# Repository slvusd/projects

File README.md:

# Projects

The purpose of this repo is to sync teacher and student work to a repo
so it can be shared and so it will not get lost.

To add a new computer to this repo, run these commands:

    git config --global user.name slvusd-gitbot
    git config --global user.email "ebrown+gitbot@slvusd.org"
    git config --global credential.helper store

Then from pi's home directory, run

    git -c credential.helper= clone https://github.com/slvusd/projects.git src

You will be prompted for the username (slvusd-github) and password. Get the
password (token) from Mr. Brown.

You need to run `$HOME/src/git_sync.sh` once from the
command line and enter the same credentials in order
to have the credentials cached for cron.

Finally, run `crontab -e` and add the following entry:

    */5 * * * * /home/pi/src/git_sync.sh

That's it!

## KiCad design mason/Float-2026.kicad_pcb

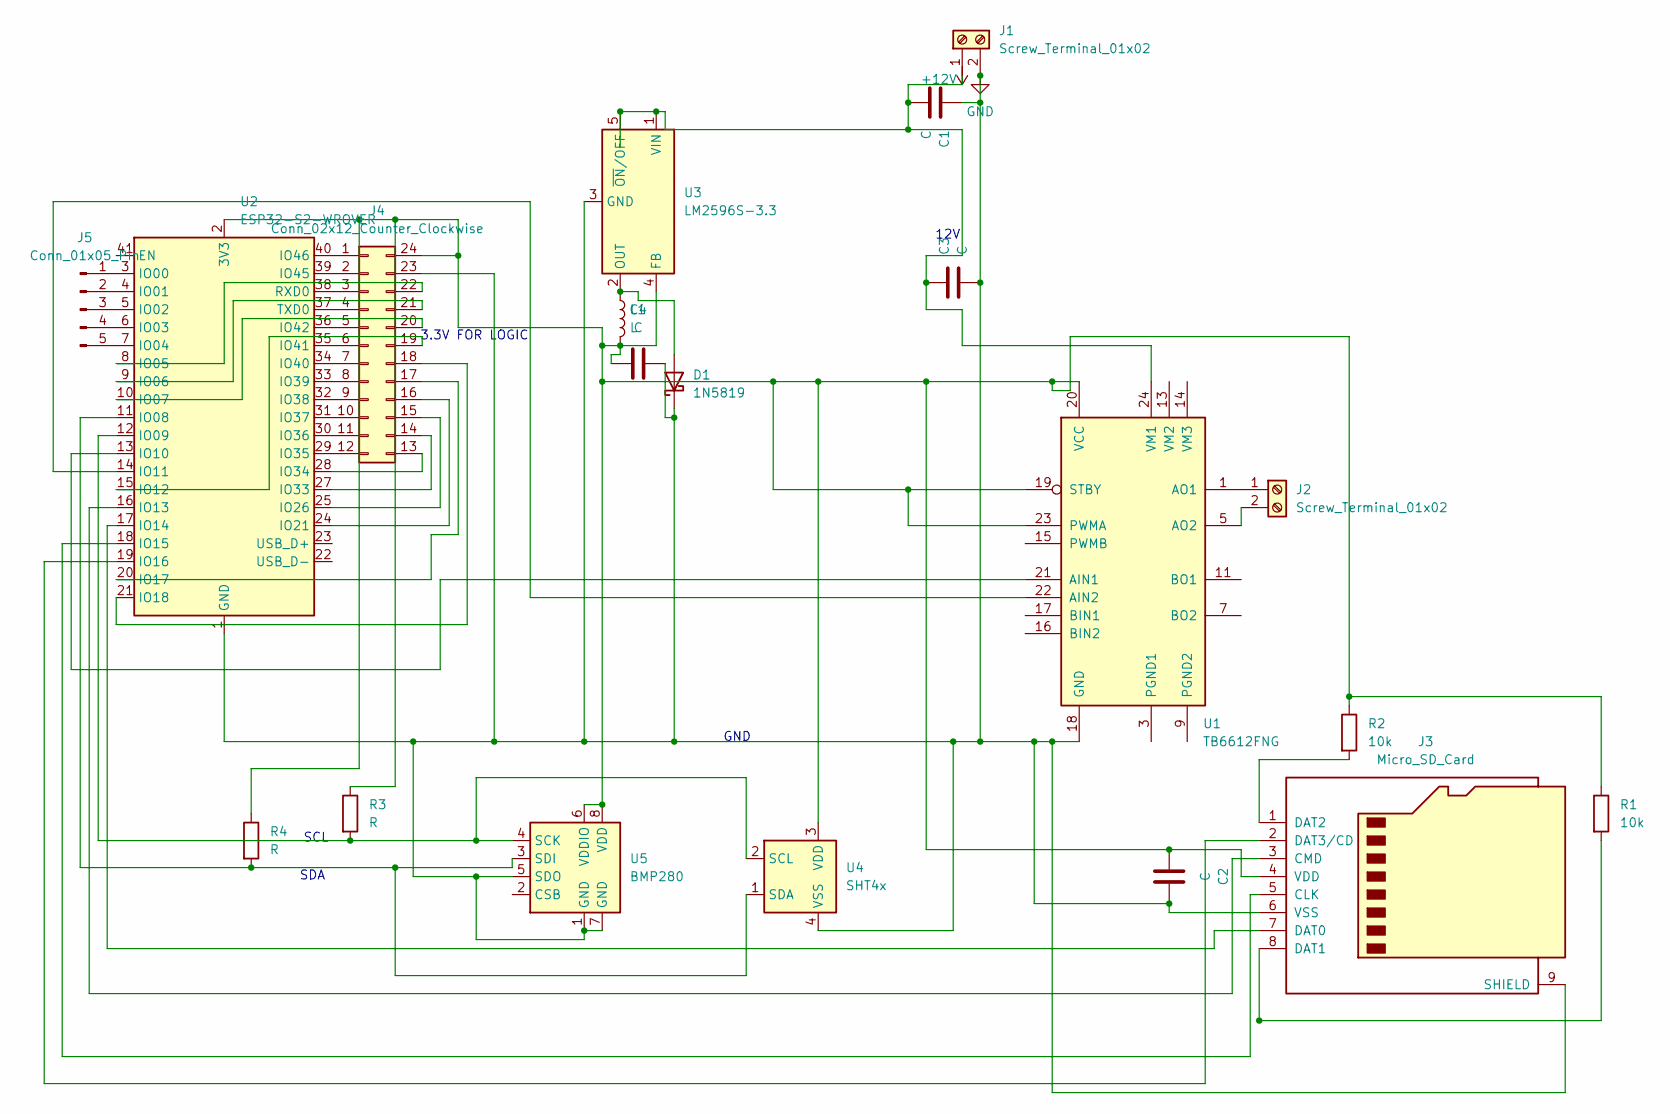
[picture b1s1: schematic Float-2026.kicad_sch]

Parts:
C1, C2, C3, C4: C; C_Axial_L3.8mm_D2.6mm_P7.50mm_Horizontal
D1: 1N5819; D_DO-41_SOD81_P10.16mm_Horizontal
J1, J2: Screw_Terminal_01x02; TerminalBlock_Ningbo-Kagnex_HB9500M_1x02_P9.5mm
J3: Micro_SD_Card; microSD_HC_Wuerth_693072010801
J4: Conn_02x12_Counter_Clockwise; PinHeader_2x12_P2.00mm_Vertical
J5: Conn_01x05_Pin; PinHeader_1x05_P2.00mm_Vertical
L1: L; L_Axial_L5.0mm_D3.6mm_P10.00mm_Horizontal_Murata_BL01RN1A2A2
R1, R2: 10k; R_Axial_DIN0204_L3.6mm_D1.6mm_P1.90mm_Vertical
R3, R4: R; R_Axial_DIN0204_L3.6mm_D1.6mm_P1.90mm_Vertical
U1: TB6612FNG; SSOP-24_5.3x8.2mm_P0.65mm
U2: ESP32-S2-WROVER
U3: LM2596S-3.3; TO-263-5_TabPin3
U4: SHT4x; Sensirion_DFN-4_1.5x1.5mm_P0.8mm_SHT4x_NoCentralPad
U5: BMP280; Bosch_LGA-8_2x2.5mm_P0.65mm_ClockwisePinNumbering

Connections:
GND: C1.1, C2.2, C3.2, C4.2, D1.1 (K), J1.2, J3.6 (VSS), J3.9 (SHIELD), J4.23, U1.18 (GND), U2.1 (GND), U2.26 (GND), U2.42 (GND), U2.43 (GND), U3.3 (GND), U4.4 (VSS), U5.1 (GND), U5.5 (SDO), U5.7 (GND)
unnamed: D1.2 (A), L1.1, U3.2 (OUT)
unnamed: C1.2, C3.1, J1.1, U1.24 (VM1), U3.1 (VIN), U3.5 (~ON/OFF)
unnamed: J2.1, U1.1 (AO1), U1.2 (AO1)
unnamed: J2.2, U1.5 (AO2), U1.6 (AO2)
unnamed: J3.5 (CLK), U2.18 (IO15)
unnamed: J3.3 (CMD), U2.16 (IO13)
unnamed: J3.7 (DAT0), U2.17 (IO14)
unnamed: J3.8 (DAT1), R1.2
unnamed: J3.1 (DAT2), R2.2
unnamed: J3.2 (DAT3/CD), U2.19 (IO16)
unnamed: C2.1, C4.1, J3.4 (VDD), J4.24, L1.2, R1.1, R2.1, R3.1, R4.1, U1.19 (STBY), U1.20 (VCC), U1.23 (PWMA), U2.2 (3V3), U3.4 (FB), U4.3 (VDD), U5.6 (VDDIO), U5.8 (VDD)
unnamed: J4.1, U2.40 (IO46)
unnamed: J4.2, U2.39 (IO45)
unnamed: J4.3, U2.38 (RXD0)
unnamed: J4.4, U2.37 (TXD0)
unnamed: J4.5, U2.36 (IO42)
unnamed: J4.6, U2.35 (IO41)
unnamed: J4.7, U2.34 (IO40)
unnamed: J4.8, U2.33 (IO39)
unnamed: J4.9, U2.32 (IO38)
unnamed: J4.10, U2.31 (IO37)
unnamed: J4.11, U2.30 (IO36)
unnamed: J4.12, U2.29 (IO35)
unnamed: J4.13, U2.28 (IO34)
unnamed: J4.14, U2.27 (IO33)
unnamed: J4.15, U2.25 (IO26)
unnamed: J4.16, U2.24 (IO21)
unnamed: J4.17, U2.20 (IO17)
unnamed: J4.18, U2.21 (IO18)
unnamed: J4.19, U2.15 (IO12)
unnamed: J4.20, U2.10 (IO07)
unnamed: J4.21, U2.9 (IO06)
unnamed: J4.22, U2.8 (IO05)
unnamed: J5.1, U2.3 (IO00)
unnamed: J5.2, U2.4 (IO01)
unnamed: J5.3, U2.5 (IO02)
unnamed: J5.4, U2.6 (IO03)
unnamed: J5.5, U2.7 (IO04)
unnamed: U1.21 (AIN1), U2.13 (IO10)
unnamed: U1.22 (AIN2), U2.14 (IO11)
unnamed: U1.11 (BO1), U1.12 (BO1)
unnamed: U1.7 (BO2), U1.8 (BO2)
unnamed: U1.3 (PGND1), U1.4 (PGND1)
unnamed: U1.9 (PGND2), U1.10 (PGND2)
unnamed: R4.2, U2.11 (IO08), U4.1 (SDA), U5.3 (SDI)
unnamed: R3.2, U2.12 (IO09), U4.2 (SCL), U5.4 (SCK)

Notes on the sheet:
SCL
12V
GND
SDA
3.3V FOR LOGIC

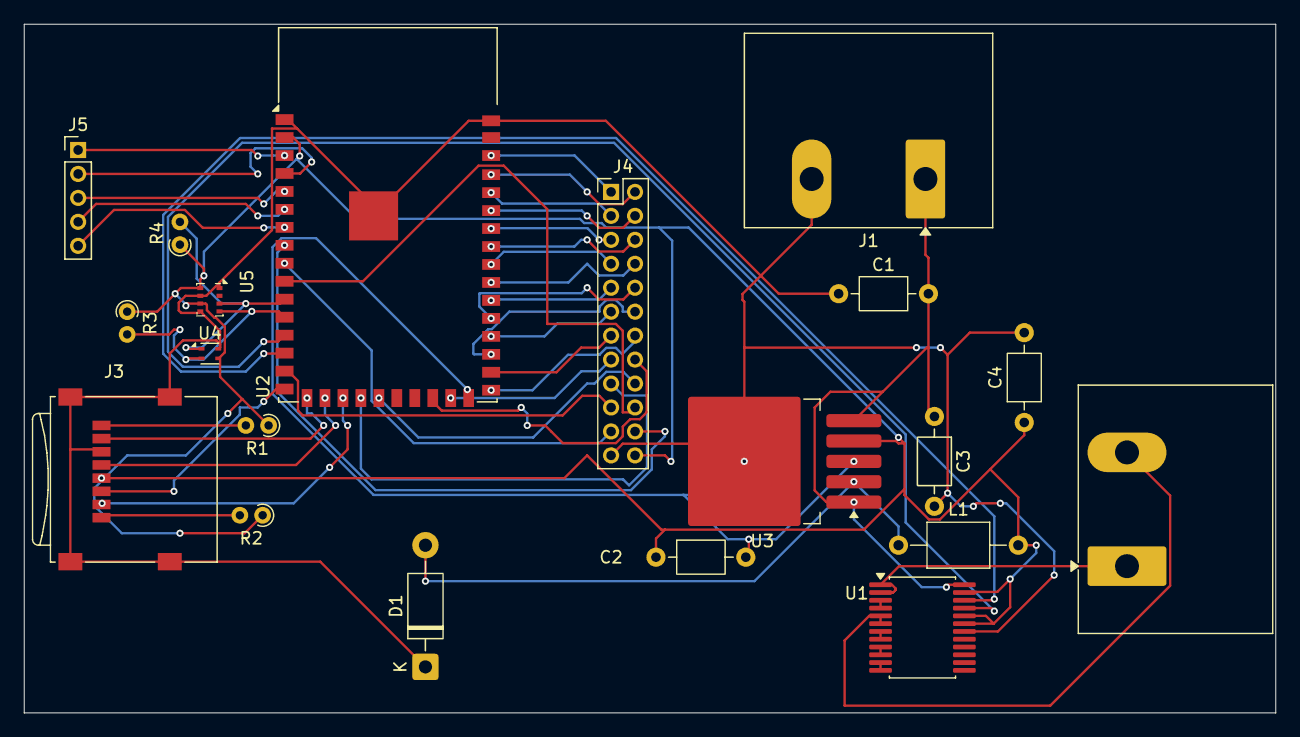
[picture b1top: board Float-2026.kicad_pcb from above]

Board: 2 copper layers, 104.5 x 57.5 mm, 20 parts (0 on the bottom side), 47 nets.

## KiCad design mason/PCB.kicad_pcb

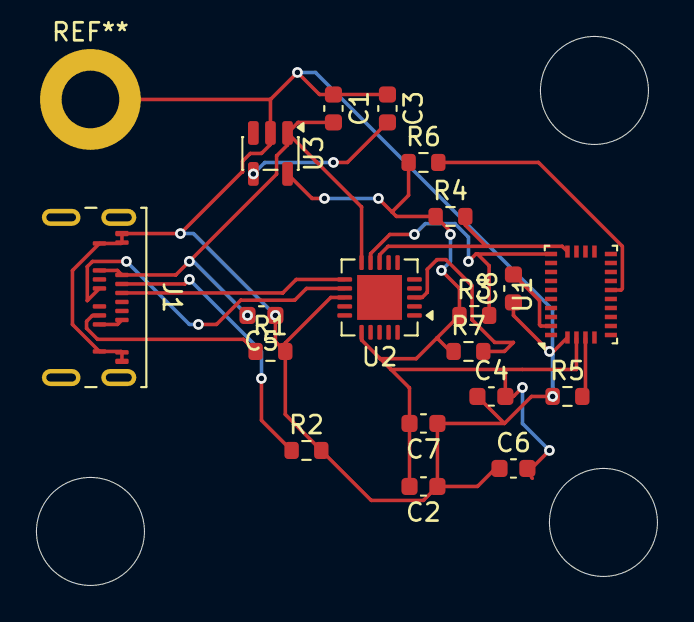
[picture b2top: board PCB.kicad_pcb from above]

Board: 2 copper layers, 34.5 x 30.5 mm, 19 parts (0 on the bottom side), 14 nets.

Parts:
C1, C2: 1µF; C_0603_1608Metric
C3: 100nF; C_0603_1608Metric
C4: 10µF; C_0603_1608Metric
C5, C6, C7, C8: 0.1µF; C_0603_1608Metric
J1: USB_C_Receptacle_USB2.0_14P; USB_C_Receptacle_Amphenol_124019772112A
R1, R2: 5.1k; R_0603_1608Metric
R3, R4: 4.7k; R_0603_1608Metric
R5, R6, R7: 10k; R_0603_1608Metric
U1: BNO055; LGA-28_5.2x3.8mm_P0.5mm
U2: MCP2221AxML; QFN-20-1EP_4x4mm_P0.5mm_EP2.5x2.5mm
U3: LP2985-3.3; SOT-23-5

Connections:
unnamed: C1.1, C2.1, C3.1, C4.1, C5.1, C6.1, C7.1, C8.1, J1.A1 (GND), J1.A12 (GND), J1.B1 (GND), J1.B12 (GND), R1.2, R2.2, R5.1, U1.2 (GND), U2.13 (VSS), U3.2 (GND)
unnamed: J1.A5 (CC1), R2.1
unnamed: J1.B5 (CC2), R1.1
unnamed: R3.2, U1.20 (COM0), U2.9 (SCL)
unnamed: R4.2, U1.19 (COM1), U2.8 (SDA)
unnamed: C2.2, C4.2, C6.2, C7.2, R3.1, R4.1, R6.1, R7.1, U1.3 (VDD), U2.16 (VDD), U3.5 (VOUT)
unnamed: C8.2, U1.28 (VDDIO)
unnamed: R5.2, U1.4 (~BOOT_LOAD_PIN)
unnamed: R6.2, U1.11 (~RESET)
unnamed: J1.B7 (D-), U2.12 (D+)
unnamed: J1.A6 (D+), U2.11 (D-)
unnamed: C1.2, C5.2, J1.A4 (VBUS), J1.A9 (VBUS), J1.B4 (VBUS), J1.B9 (VBUS), U2.10 (VUSB), U3.1 (VIN)
unnamed: R7.2, U2.3 (~RST)
unnamed: C3.2, U3.4 (BP)

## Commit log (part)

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2024-11-22 Auto-sync: Thu 21 Nov 21:04:49 PST 2024
2024-11-22 Update README.md
    Add instructions for adding new computers.
2024-11-22 Auto-sync: Thu 21 Nov 21:25:02 PST 2024
2024-11-22 Auto-sync: Thu 21 Nov 22:15:02 PST 2024
2024-11-22 Auto-sync: Thu 21 Nov 22:17:30 PST 2024
2024-11-22 Update instructions
2024-11-22 Auto-sync: Fri 22 Nov 13:15:03 PST 2024
2024-11-25 Auto-sync: Mon 25 Nov 00:40:01 PST 2024
2024-11-25 Auto-sync: Mon 25 Nov 00:50:02 PST 2024
2024-11-25 Auto-sync: Mon 25 Nov 00:55:01 PST 2024
2024-11-25 Auto-sync: Mon 25 Nov 01:00:02 PST 2024
2024-11-25 Auto-sync: Mon 25 Nov 01:05:01 PST 2024
2024-11-25 Auto-sync: Mon 25 Nov 01:10:01 PST 2024
2024-11-25 Auto-sync: Mon 25 Nov 01:15:02 PST 2024
2024-11-25 Auto-sync: Mon 25 Nov 01:25:01 PST 2024
2024-11-25 Auto-sync: Mon 25 Nov 01:30:02 PST 2024
2024-11-25 Auto-sync: Mon 25 Nov 01:35:19 PST 2024
2024-11-25 Auto-sync: Mon 25 Nov 02:05:02 PST 2024
2024-11-25 Auto-sync: Mon 25 Nov 02:10:02 PST 2024
2024-11-25 Auto-sync: Mon 25 Nov 02:15:02 PST 2024
2024-11-25 Auto-sync: Mon 25 Nov 02:20:02 PST 2024
2024-11-25 Auto-sync: Mon 25 Nov 02:45:02 PST 2024
2024-11-25 Auto-sync: Mon 25 Nov 02:50:02 PST 2024
2024-11-25 Auto-sync: Mon 25 Nov 02:55:02 PST 2024
2024-11-25 Auto-sync: Mon 25 Nov 03:00:02 PST 2024
2024-11-25 Auto-sync: Mon 25 Nov 03:05:02 PST 2024
2024-11-25 Auto-sync: Mon 25 Nov 03:10:02 PST 2024
2024-11-25 Auto-sync: Mon 25 Nov 03:15:02 PST 2024
2024-11-26 Auto-sync from slvpi3-1: Mon 25 Nov 16:20:03 PST 2024
2024-11-26 Auto-sync from slvpi3-1: Mon 25 Nov 16:30:02 PST 2024
2024-11-26 Auto-sync from slvpi3-1: Mon 25 Nov 16:35:02 PST 2024
2024-11-26 Auto-sync from slvpi3-1: Mon 25 Nov 16:40:03 PST 2024
2024-11-26 Auto-sync from slvpi4-2: Mon 25 Nov 17:05:03 PST 2024
2024-11-26 Auto-sync from slvpi4-2: Mon 25 Nov 17:10:02 PST 2024
2024-11-26 Auto-sync from slvpi4-2: Mon 25 Nov 17:55:02 PST 2024
2024-11-26 Auto-sync from slvpi3-1: Mon 25 Nov 18:00:03 PST 2024
2024-11-26 Auto-sync from slvpi3-1: Mon 25 Nov 18:05:02 PST 2024
2024-11-26 Auto-sync from slvpi3-1: Mon 25 Nov 18:10:02 PST 2024
2024-11-26 Auto-sync from slvpi3-1: Mon 25 Nov 18:15:02 PST 2024
2024-11-26 Auto-sync from slvpi3-1: Mon 25 Nov 18:20:02 PST 2024
2024-11-26 Auto-sync from slvpi4-2: Mon 25 Nov 18:36:52 PST 2024
2024-11-26 Auto-sync from slvpi4-2: Mon 25 Nov 18:45:02 PST 2024
2024-11-26 Auto-sync from slvpi4-2: Mon 25 Nov 18:50:02 PST 2024
2024-11-26 Auto-sync from slvpi4-2: Mon 25 Nov 19:05:01 PST 2024
2024-11-26 Auto-sync from slvpi4-2: Mon 25 Nov 20:35:03 PST 2024
2024-11-26 Auto-sync from slvpi4-2: Mon 25 Nov 20:40:02 PST 2024
2024-11-26 Auto-sync from slvpi4-2: Mon 25 Nov 20:55:02 PST 2024
2024-11-26 Auto-sync from slvpi4-2: Mon 25 Nov 21:00:02 PST 2024
2024-11-26 Auto-sync from slvpi4-2: Mon 25 Nov 21:10:02 PST 2024
2024-11-26 Auto-sync from slvpi4-2: Mon 25 Nov 21:15:01 PST 2024
2024-11-26 Auto-sync from slvpi4-2: Mon 25 Nov 21:20:02 PST 2024
2024-11-26 Auto-sync from slvpi4-2: Mon 25 Nov 21:25:01 PST 2024
2024-11-26 Auto-sync from slvpi4-2: Mon 25 Nov 21:30:02 PST 2024
2024-11-26 Auto-sync from slvpi3-1: Tue 26 Nov 12:25:02 PST 2024
2024-11-26 Auto-sync from slvpi3-1: Tue 26 Nov 12:30:04 PST 2024
2024-11-26 Auto-sync from slvpi3-1: Tue 26 Nov 12:40:02 PST 2024
2024-11-26 Auto-sync from slvpi3-1: Tue 26 Nov 12:45:02 PST 2024
2024-11-26 Auto-sync from slvpi3-1: Tue 26 Nov 12:55:03 PST 2024
2024-11-26 Auto-sync from slvpi3-1: Tue 26 Nov 13:00:03 PST 2024
2024-11-26 Auto-sync from slvpi3-1: Tue 26 Nov 13:10:04 PST 2024
2024-11-26 Auto-sync from slvpi3-1: Tue 26 Nov 13:25:02 PST 2024
2024-11-26 Auto-sync from slvpi3-1: Tue 26 Nov 13:30:02 PST 2024
2024-11-26 Auto-sync from slvpi3-1: Tue 26 Nov 13:55:02 PST 2024
2024-11-26 Auto-sync from slvpi3-1: Tue 26 Nov 14:05:02 PST 2024
2024-11-26 Auto-sync from slvpi3-1: Tue 26 Nov 14:10:02 PST 2024
2024-11-26 Auto-sync from slvpi3-1: Tue 26 Nov 14:25:02 PST 2024
2024-11-27 Auto-sync from slvpi4-2: Tue 26 Nov 18:35:02 PST 2024
2024-11-27 Auto-sync from slvpi4-2: Tue 26 Nov 21:45:03 PST 2024
2024-11-27 Auto-sync from slvpi4-2: Tue 26 Nov 21:55:02 PST 2024
2024-11-27 Auto-sync from slvpi4-2: Tue 26 Nov 22:00:02 PST 2024
2024-11-27 Documentaiton based on today's work
2024-11-27 Auto-sync from slvpi5: Wed 27 Nov 09:35:02 PST 2024
2024-11-27 Auto-sync from slvpi5: Wed 27 Nov 09:40:01 PST 2024
2024-11-28 Auto-sync from slvpi4-2: Wed 27 Nov 22:20:05 PST 2024
2024-11-28 Auto-sync from slvpi4-2: Wed 27 Nov 22:25:02 PST 2024
2024-11-28 Auto-sync from slvpi4-2: Wed 27 Nov 22:35:02 PST 2024
2024-11-28 Auto-sync from slvpi4-2: Wed 27 Nov 22:40:02 PST 2024
2024-11-29 Add circuit diagram to variable_motor
2024-11-30 Auto-sync from slvpizt1: Sat 30 Nov 10:40:19 PST 2024
2024-11-30 Auto-sync from slvpizt1: Sat 30 Nov 10:45:04 PST 2024
2024-11-30 Auto-sync from slvpizt1: Sat 30 Nov 10:50:04 PST 2024
2024-11-30 Auto-sync from slvpizt1: Sat 30 Nov 11:15:03 PST 2024
2024-11-30 Auto-sync from slvpizt1: Sat 30 Nov 11:25:12 PST 2024
2024-11-30 Auto-sync from slvpizt1: Sat 30 Nov 11:30:04 PST 2024
2024-11-30 Auto-sync from slvpizt1: Sat 30 Nov 11:35:05 PST 2024
2024-11-30 Auto-sync from slvpizt1: Sat 30 Nov 11:40:11 PST 2024
2024-11-30 Auto-sync from slvpizt1: Sat 30 Nov 13:10:10 PST 2024
2024-12-01 Auto-sync from slvpizt1: Sun 1 Dec 08:55:05 PST 2024
2024-12-02 Auto-sync from slvpi5: Sun 1 Dec 17:05:01 PST 2024
2024-12-09 Auto-sync from slvpi4-2: Mon 9 Dec 13:40:05 PST 2024
2024-12-09 Auto-sync from slvpi4-2: Mon 9 Dec 13:45:04 PST 2024
2024-12-09 Auto-sync from slvpi4-2: Mon 9 Dec 13:50:04 PST 2024
2024-12-09 Auto-sync from slvpi4-2: Mon 9 Dec 13:55:05 PST 2024
2024-12-10 Auto-sync from slvpi4-2: Tue 10 Dec 13:50:09 PST 2024
2024-12-10 Auto-sync from slvpi4-2: Tue 10 Dec 14:00:06 PST 2024
2024-12-10 Auto-sync from slvpi4-2: Tue 10 Dec 14:05:04 PST 2024
2024-12-10 Auto-sync from slvpi4-2: Tue 10 Dec 14:45:04 PST 2024
2024-12-10 Auto-sync from slvpi4-2: Tue 10 Dec 14:50:04 PST 2024
2024-12-11 Auto-sync from slvpi4-2: Tue 10 Dec 17:35:16 PST 2024
2024-12-11 Auto-sync from slvpizt1: Tue 10 Dec 17:40:02 PST 2024
2024-12-13 Auto-sync from slvpi4-2: Fri 13 Dec 09:35:03 PST 2024
2024-12-13 Auto-sync from slvpi4-2: Fri 13 Dec 14:35:04 PST 2024
2024-12-13 Auto-sync from slvpi4-2: Fri 13 Dec 14:50:05 PST 2024
2024-12-25 Auto-sync from slvpi5: Wed 25 Dec 13:55:01 PST 2024
2024-12-25 Auto-sync from slvpi5: Wed 25 Dec 14:00:02 PST 2024
2025-01-16 Auto-sync from slvpi4-2: Thu 16 Jan 14:35:04 PST 2025
2025-01-16 Auto-sync from slvpi4-2: Thu 16 Jan 14:40:04 PST 2025
2025-01-16 Auto-sync from slvpi4-2: Thu 16 Jan 14:45:09 PST 2025
2025-01-21 Auto-sync from slvpi4-2: Tue 21 Jan 11:40:05 PST 2025
2025-01-21 Auto-sync from slvpi4-2: Tue 21 Jan 12:55:04 PST 2025
2025-01-21 Auto-sync from slvpi4-2: Tue 21 Jan 13:05:04 PST 2025
2025-01-21 Auto-sync from slvpi4-2: Tue 21 Jan 13:55:04 PST 2025
2025-01-21 Auto-sync from slvpi4-2: Tue 21 Jan 14:00:04 PST 2025
2025-01-21 Auto-sync from slvpi4-2: Tue 21 Jan 14:05:04 PST 2025
2025-01-21 Auto-sync from slvpi4-2: Tue 21 Jan 14:10:04 PST 2025
2025-01-21 Auto-sync from slvpi4-2: Tue 21 Jan 14:25:04 PST 2025
2025-01-21 Auto-sync from slvpi4-2: Tue 21 Jan 14:35:04 PST 2025
2025-01-21 Auto-sync from slvpi4-2: Tue 21 Jan 14:40:04 PST 2025
2025-01-21 Auto-sync from slvpi4-2: Tue 21 Jan 14:45:04 PST 2025
2025-01-21 Auto-sync from slvpi4-2: Tue 21 Jan 14:50:04 PST 2025
2025-01-23 Auto-sync from slvpi4-2: Thu 23 Jan 12:50:06 PST 2025
2025-01-23 Auto-sync from slvpi4-2: Thu 23 Jan 12:55:05 PST 2025
2025-01-23 Auto-sync from slvpi4-2: Thu 23 Jan 13:00:04 PST 2025
2025-01-23 Auto-sync from slvpi4-2: Thu 23 Jan 13:55:04 PST 2025
2025-01-23 Auto-sync from slvpi4-2: Thu 23 Jan 14:00:06 PST 2025
2025-01-23 Auto-sync from slvpi4-2: Thu 23 Jan 14:05:04 PST 2025
2025-01-23 Auto-sync from slvpi4-2: Thu 23 Jan 14:10:04 PST 2025
2025-01-23 Auto-sync from slvpi4-2: Thu 23 Jan 14:25:04 PST 2025
2025-01-23 Auto-sync from slvpi4-2: Thu 23 Jan 14:30:04 PST 2025
2025-01-23 Auto-sync from slvpi4-2: Thu 23 Jan 14:45:04 PST 2025
2025-01-24 Auto-sync from slvpi4-2: Fri 24 Jan 13:00:04 PST 2025
2025-01-24 Auto-sync from slvpi4-2: Fri 24 Jan 13:10:04 PST 2025
2025-01-24 Auto-sync from slvpi4-2: Fri 24 Jan 13:15:04 PST 2025
2025-01-24 Auto-sync from slvpi4-2: Fri 24 Jan 13:20:04 PST 2025
2025-01-24 Auto-sync from slvpi4-2: Fri 24 Jan 13:25:04 PST 2025
2025-01-24 Auto-sync from slvpi4-2: Fri 24 Jan 13:30:06 PST 2025
2025-01-24 Auto-sync from slvpi4-2: Fri 24 Jan 13:40:05 PST 2025
2025-01-24 Auto-sync from slvpi4-2: Fri 24 Jan 13:45:05 PST 2025
2025-01-24 Auto-sync from slvpi4-2: Fri 24 Jan 14:45:04 PST 2025
2025-01-24 Auto-sync from slvpi4-2: Fri 24 Jan 14:50:04 PST 2025
2025-01-31 Auto-sync from slvpi4-2: Fri 31 Jan 13:10:05 PST 2025
2025-01-31 Auto-sync from slvpi4-2: Fri 31 Jan 13:15:05 PST 2025
2025-01-31 Auto-sync from slvpi4-2: Fri 31 Jan 13:40:04 PST 2025
2025-01-31 Auto-sync from slvpi4-2: Fri 31 Jan 14:05:04 PST 2025
2025-01-31 Auto-sync from slvpi4-2: Fri 31 Jan 14:50:05 PST 2025
2025-02-03 Auto-sync from slvpi4-2: Mon 3 Feb 13:20:04 PST 2025
2025-02-03 Auto-sync from slvpi4-2: Mon 3 Feb 13:25:04 PST 2025
2025-02-03 Auto-sync from slvpi4-2: Mon 3 Feb 13:35:06 PST 2025
2025-02-03 Auto-sync from slvpi4-2: Mon 3 Feb 13:40:05 PST 2025
2025-02-03 Auto-sync from slvpi4-2: Mon 3 Feb 13:45:04 PST 2025
2025-02-03 Auto-sync from slvpi4-2: Mon 3 Feb 13:55:09 PST 2025
2025-04-30 Auto-sync from slvpi4-2: Wed 30 Apr 14:00:04 PDT 2025
2025-04-30 Auto-sync from slvpi4-2: Wed 30 Apr 14:05:04 PDT 2025
2025-04-30 Auto-sync from slvpi4-2: Wed 30 Apr 14:20:04 PDT 2025
2025-05-28 Auto-sync from slvpi4-2: Wed 28 May 12:55:05 PDT 2025
2025-05-28 Auto-sync from slvpi4-2: Wed 28 May 13:00:04 PDT 2025
2025-05-28 Auto-sync from slvpi4-2: Wed 28 May 13:05:04 PDT 2025
2026-01-19 Auto-sync from pi47: Mon 19 Jan 13:40:02 PST 2026
2026-01-20 Auto-sync from piz0: Mon 19 Jan 21:00:03 PST 2026
2026-01-20 Auto-sync from pi07: Mon Jan 19 21:05:12 PST 2026
2026-01-20 Auto-sync from pi07: Mon Jan 19 21:10:14 PST 2026
2026-01-20 Auto-sync from pi07: Mon Jan 19 21:15:06 PST 2026
2026-01-20 Auto-sync from pi07: Mon Jan 19 21:25:06 PST 2026
2026-01-20 Auto-sync from pi07: Mon Jan 19 21:40:07 PST 2026
2026-01-20 Auto-sync from pi07: Mon Jan 19 22:00:18 PST 2026
2026-01-20 Auto-sync from pi07: Mon Jan 19 22:05:10 PST 2026
2026-01-20 Auto-sync from pi07: Mon Jan 19 22:10:10 PST 2026
2026-01-20 Auto-sync from pi07: Mon Jan 19 22:30:11 PST 2026
2026-01-20 Auto-sync from pi07: Mon Jan 19 22:35:08 PST 2026
2026-01-20 Auto-sync from pi07: Tue Jan 20 14:55:04 PST 2026
2026-01-20 Auto-sync from pi07: Tue Jan 20 15:35:03 PST 2026
2026-01-20 Auto-sync from pi07: Tue Jan 20 15:45:03 PST 2026
2026-01-20 Auto-sync from pi07: Tue Jan 20 15:55:03 PST 2026
2026-01-21 Auto-sync from pi07: Tue Jan 20 16:35:03 PST 2026
2026-01-21 Auto-sync from pi07: Tue Jan 20 16:55:05 PST 2026
2026-02-04 Update joy.py
    Fix "bugs" for future reference
2026-02-04 Create joy11.py
    Fully functioning and calibrated(?) computation and input for 2 joysticks moving 6 motors 4 at 45 degrees more movement and 2 for vertical and roll control.
2026-02-05 Create joyREFERENCE.py (ish)
    I need a life.... this is bad now
2026-02-06 Create Joy mac thingy
2026-02-06 Create Sonar??? i need a life
2026-02-06 Create Sonar test(4 windows only i think)
2026-02-25 Added PCB files
    Finished PCB to have accelerometer go directly to USBC data ports for ease of use
    (You're welcome)
2026-03-06 Auto-sync from pi07: Thu Mar 5 16:20:04 PST 2026
2026-03-06 Auto-sync from pi07: Thu Mar 5 16:25:10 PST 2026
2026-03-06 Auto-sync from pi07: Thu Mar 5 16:40:05 PST 2026
2026-03-06 Create FLOAT
    unfinished
2026-03-10 Auto-sync from pi07: Tue Mar 10 15:35:04 PDT 2026
2026-03-10 Auto-sync from pi07: Tue Mar 10 15:40:04 PDT 2026
2026-03-10 Auto-sync from pi07: Tue Mar 10 16:30:04 PDT 2026
2026-03-10 Auto-sync from pi07: Tue Mar 10 16:45:06 PDT 2026
2026-03-10 Auto-sync from pi07: Tue Mar 10 16:50:06 PDT 2026
2026-03-11 Auto-sync from pi07: Tue Mar 10 17:05:04 PDT 2026
2026-03-11 Auto-sync from pi07: Tue Mar 10 17:20:04 PDT 2026
2026-03-12 Auto-sync from pi07: Thu Mar 12 16:15:03 PDT 2026
2026-03-12 Auto-sync from pi07: Thu Mar 12 16:20:03 PDT 2026
2026-03-16 Add IMU code
